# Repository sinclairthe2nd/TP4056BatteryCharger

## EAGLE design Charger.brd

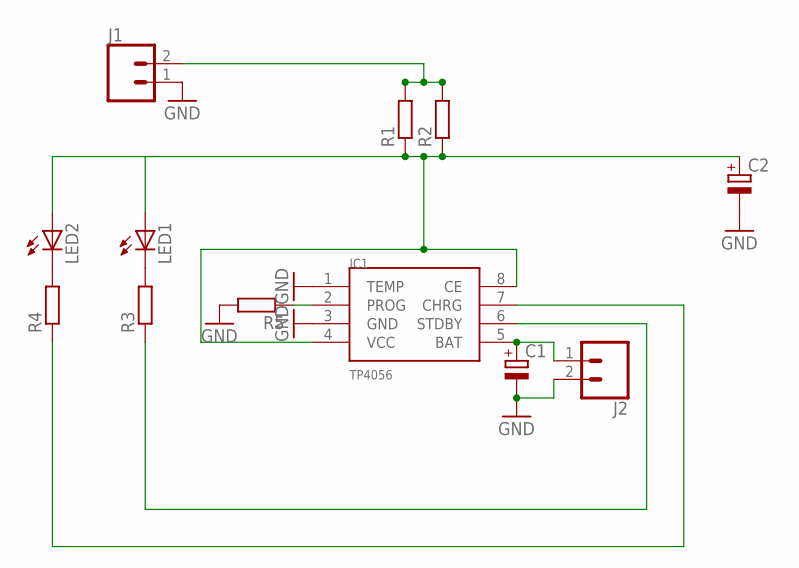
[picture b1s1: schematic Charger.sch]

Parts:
C1, C2: CPOL-EUE2.5-7; E2,5-7
IC1: TP4056; SOP-8
J1, J2: CONN_02PTH4; 1X02_XTRA_BIG
LED1, LED2: LED5MM
R1, R2, R3, R4, R5: R-EU_R1206; R1206

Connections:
GND: C1.-, C2.-, IC1.1 (TEMP), IC1.3 (GND), J1.1, J2.2, R5.2
unnamed: LED2.K (C), R4.2
unnamed: LED1.K (C), R3.2
unnamed: C1.+, IC1.5 (BAT), J2.1
unnamed: J1.2, R1.2, R2.2
unnamed: C2.+, IC1.4 (VCC), IC1.8 (CE), LED1.A, LED2.A, R1.1, R2.1
unnamed: IC1.6 (STDBY), R3.1
unnamed: IC1.7 (CHRG), R4.1
unnamed: IC1.2 (PROG), R5.1

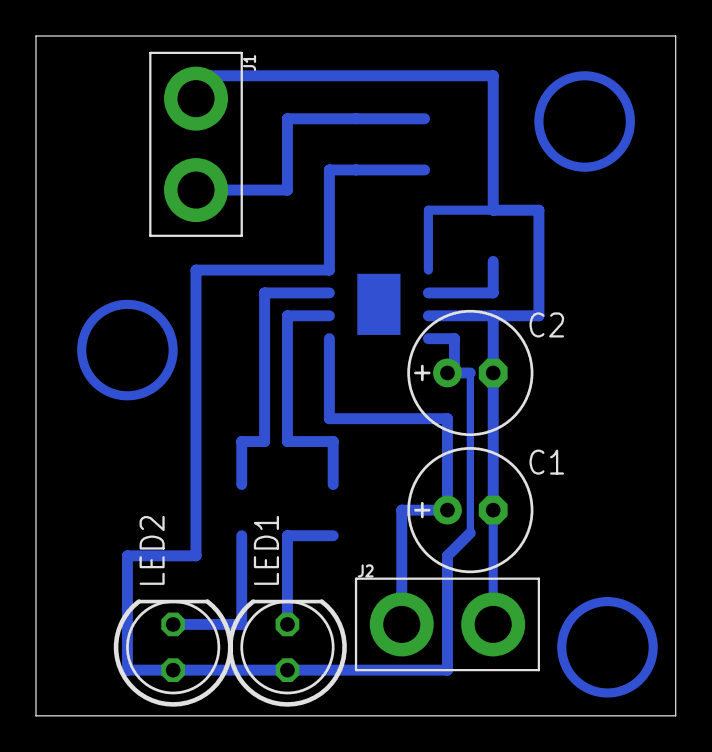
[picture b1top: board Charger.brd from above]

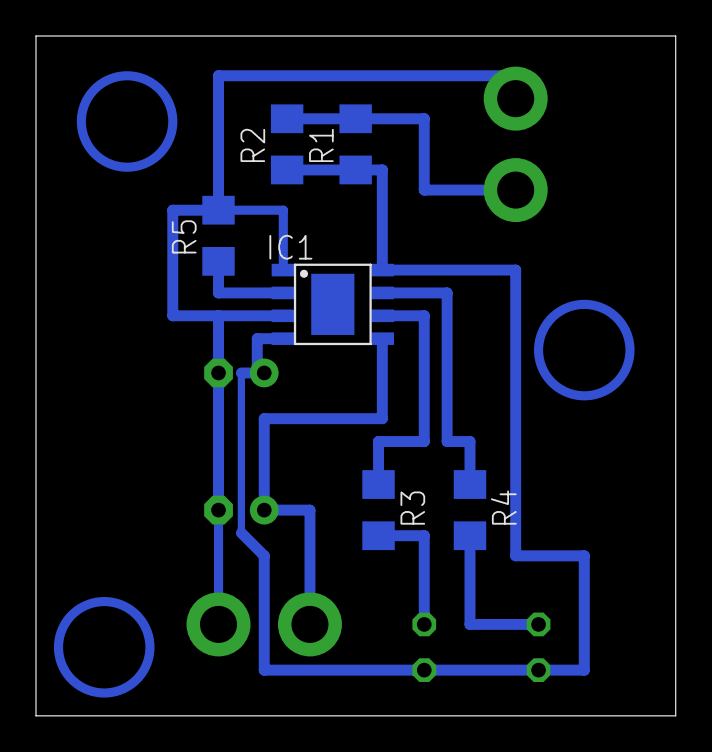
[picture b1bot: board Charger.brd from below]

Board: 2 copper layers, 35.5 x 37.8 mm, 12 parts (6 on the bottom side), 9 nets.

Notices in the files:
parts and their libraries:
SparkFun-Connectors: Licensing: Creative Commons ShareAlike 4.0 International - https://creativecommons.org/licenses/by-sa/4.0
